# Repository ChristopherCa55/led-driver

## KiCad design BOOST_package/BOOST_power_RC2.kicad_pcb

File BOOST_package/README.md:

# BOOST LED driver: design files for PCB review

A three-channel boost LED driver on two boards, designed in KiCad 10 and simulated in LTspice 26. The boards are
meant to be made and assembled by JLCPCB.

## Boards

| Board | File | Size | Layers |
|---|---|---|---|
| Power board | `KiCad/BOOST_power_RC2.kicad_pcb` | 74 x 86 mm (18 x 12 mm corner notch) | 6 (stackup JLC061611-7628D, specified at order) |
| Control card | `KiCad/BOOST_control_RC2.kicad_pcb` | 45 x 45 mm | 6 |

The schematic for both boards is `KiCad/BOOST.kicad_sch` (open `KiCad/BOOST.kicad_pro`). Each board also has its
own schematic, linked to its PCB: open `KiCad/BOOST_power_RC2.kicad_pro` or `KiCad/BOOST_control_RC2.kicad_pro`
(Switch to PCB Editor and Update PCB work there). These hold the same parts as the main schematic, so a change goes
into both. The `.pretty` folders,
`ltspice.kicad_sym`, `fp-lib-table` and `sym-lib-table` in `KiCad/` are the project's own footprint and symbol
libraries; KiCad finds them automatically.

## KiCad notes
- Each board has its own `.kicad_pro`, which carries its net classes and design rules. Open a board through (or
  beside) its own `.kicad_pro`; without it, DRC falls back to the defaults.
- 3D models: the parts use KiCad's standard 3D library (`${KICAD10_3DMODEL_DIR}`), which comes with KiCad.

## ERC and DRC
- ERC: 0 errors, 0 warnings for the main schematic and both board projects. The card schematic has PWR_FLAGs on 5V
  and GND (they reach the card only through J11); the main schematic has none there, as U17 drives 5V.
- DRC with schematic parity: 0 on both boards.
- Power board: 0 errors, 0 unconnected. The 49 warnings are expected:
  - 46 silk over copper: a top-side logo under L1 crosses L1's middle (mechanical) pad. It is hidden under L1, and
    the gerbers cut silkscreen away from exposed pads.
  - 2 silk overlaps: the can outlines of C87/C71 and C86/C88 touch.
  - 1 library mismatch: J10's holes are drilled 1.05 mm on purpose (Samtec 0.64 mm square posts).
- Control card: 0 errors, 0 unconnected. The 1 warning is expected: a library mismatch, because J11's holes are
  drilled 1.05 mm on purpose (Samtec 0.64 mm square posts).

## LTspice
`LTspice/BOOST.asc` uses:
- custom symbols: `74HC4051.asy`, `CD4017B.asy`, `CD74HC4066.asy`, `CSS4J_4026.asy`, `INA241A4.asy`, `L78L05.asy`,
  `MC7812.asy`, `MCP4451_CTRL.asy`, `MCP4451_POT.asy`, `UCC21520.asy`;
- model libraries: `74HC4051.lib`, `CD4000_v.lib`, `CD74HC4066.lib`, `CSS4J.lib`, `HYG180N10.lib`, `INA241A4.lib`,
  `L78L05.lib`, `MC7812.lib`, `MCP4451.lib`, `MCP6561.lib`, `TLV9001.lib`, `TVS_5p0SMDJ.lib`, `UCC21520.lib`.
- The INA241A4, CD74HC4066, 74HC4051, MCP4451, L78L05, MC7812, CSS4J shunt and the 5.0SMDJ54A TVS use custom
  behavioural models written for this simulation. U16 (MC7812) uses `MC7812_TYP`, the typical dropout from
  onsemi's curve (about 1.5 V); `MC7812_WC` in the same file is a pessimistic 2 V variant.
- D28-D30 (pre-charge diodes, S2MW) use an inline `.model S2MW` directive: LTspice's 1N4007 scaled to a 2 A die
  (VF 0.91 V at 2 A; data sheet max 1.1 V). Jingdao publishes no SPICE model.
- The `LED_RED`/`LED_GREEN`/`LED_BLUE` models are unused on purpose; the LEDs use the `100W_` models.
- D19 (5.0SMDJ54A) is modelled at its minimum breakdown, 60.0 V. Over 25-30 ms it conducts in 101 of 453 switching
  cycles (22 %), 9.5 mW on average (0.15 % of its 6.5 W rating); most of its current is junction capacitance at the LX
  edges. A typical part (about 63 V) would not conduct at all in steady state.

**Parameters** (a `.param` line near the other directives):
- `IREF1_DUTY`, `IREF2_DUTY`, `IREF3_DUTY`: the Arduino's IREF PWM duty in 256ths at 490 Hz. 256 = always on (the
  default), 128 = 50 %, 0 = off.
- `POT1_CODE`, `POT2_CODE`, `POT3_CODE`: the MCP4451 wiper codes of U26A/B/C (0-256). The defaults 86/103/103 give
  2.635/2.371/2.371 A LED peaks. Code 0 is full current and 256 is zero (the pot's A terminal is grounded). At
  power-up the pot sits at mid-scale (128, about 1.98 A) until the firmware writes a code.
- Parts named `SIM_...` exist only in the simulation: the battery, cable, LEDs and the Arduino outputs.

**Results:** a 30 ms run at full duty converges in about 15-50 minutes. The `.options` line carries `solver=alt`:
with the I2C pull-ups R106 / R107 in the netlist the normal solver stops at 0.3216 ms; `solver=alt` is about 3x
slower and gives the same results. Over 25-30 ms the LEDs hold 2.635, 2.371 and
2.371 A, the outputs sit at 23.3, 33.1 and 33.1 V, and LX peaks at about 61 V.

**Start-up:** the two `.ic` lines start the servos and reference filters already settled, so the LEDs reach full
brightness within about 15 ms. Delete both lines for a true cold start (full brightness takes about half a second).
That shortcut start shows one 81 V LX spike at 0.15 ms, which real hardware does not see because it starts with the
references at zero.

**PWM dimming** (`IREFn_DUTY` below 256): each pulse keeps the full current down to about 19 % duty (red) and 25 %
(green, blue); below that the pulses carry less current. Runs can stall while all LEDs are off; the `solver=alt`
on the `.options` line gets past that.

**File size:** LTspice saves every node, so a 30 ms run writes about 22 GB (`BOOST.raw`). Make sure there is room,
or add a `.save` line that lists only the signals you want.

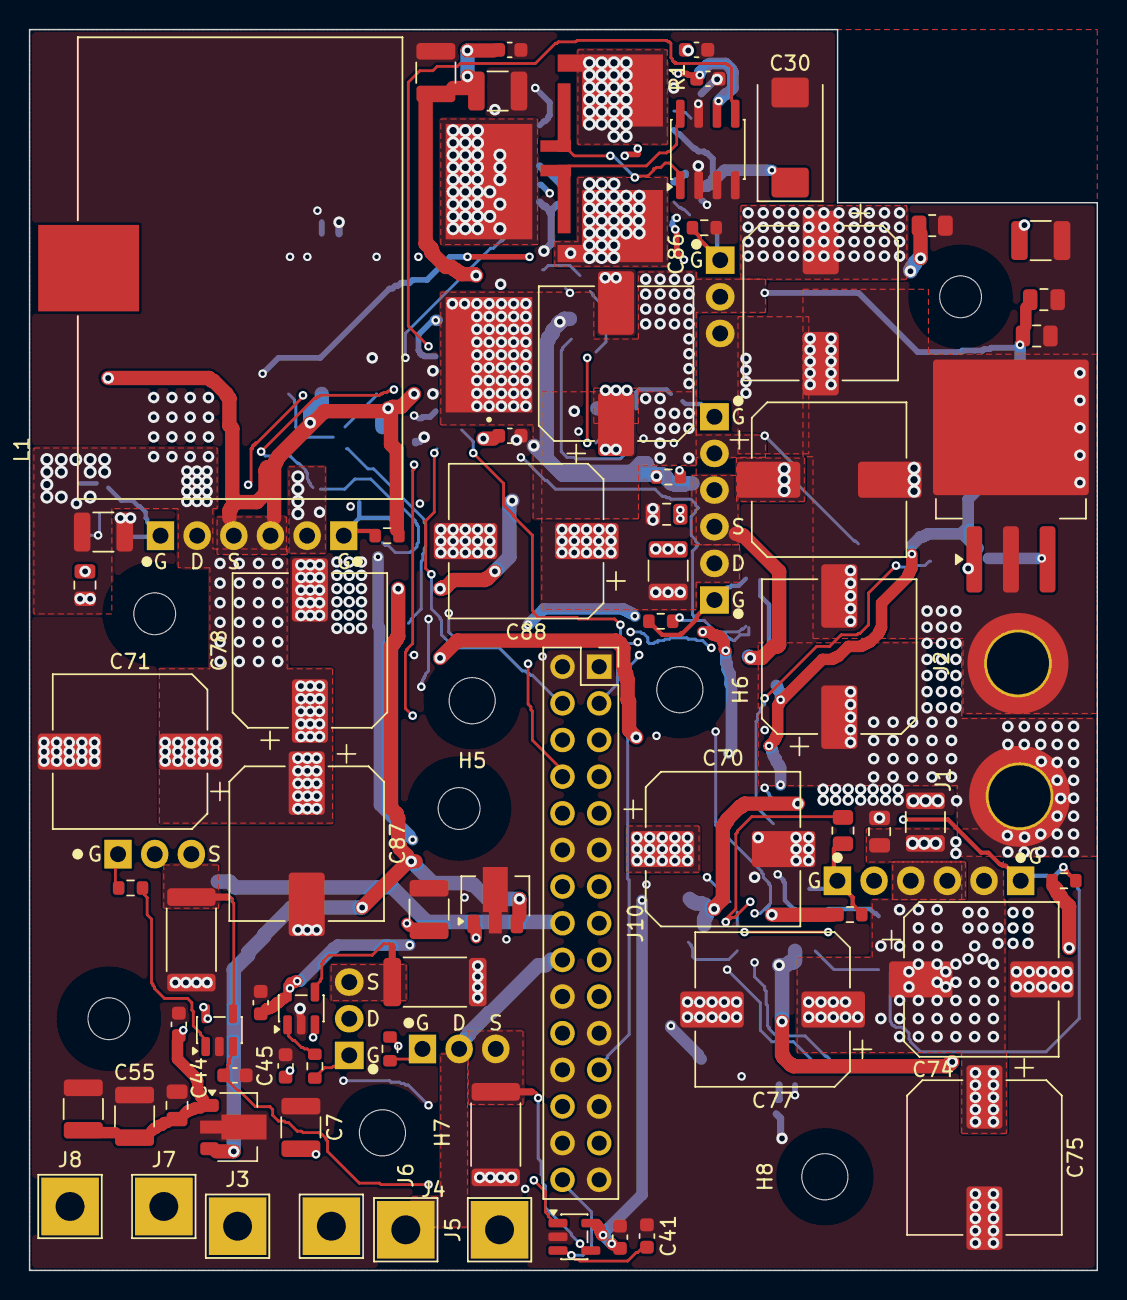
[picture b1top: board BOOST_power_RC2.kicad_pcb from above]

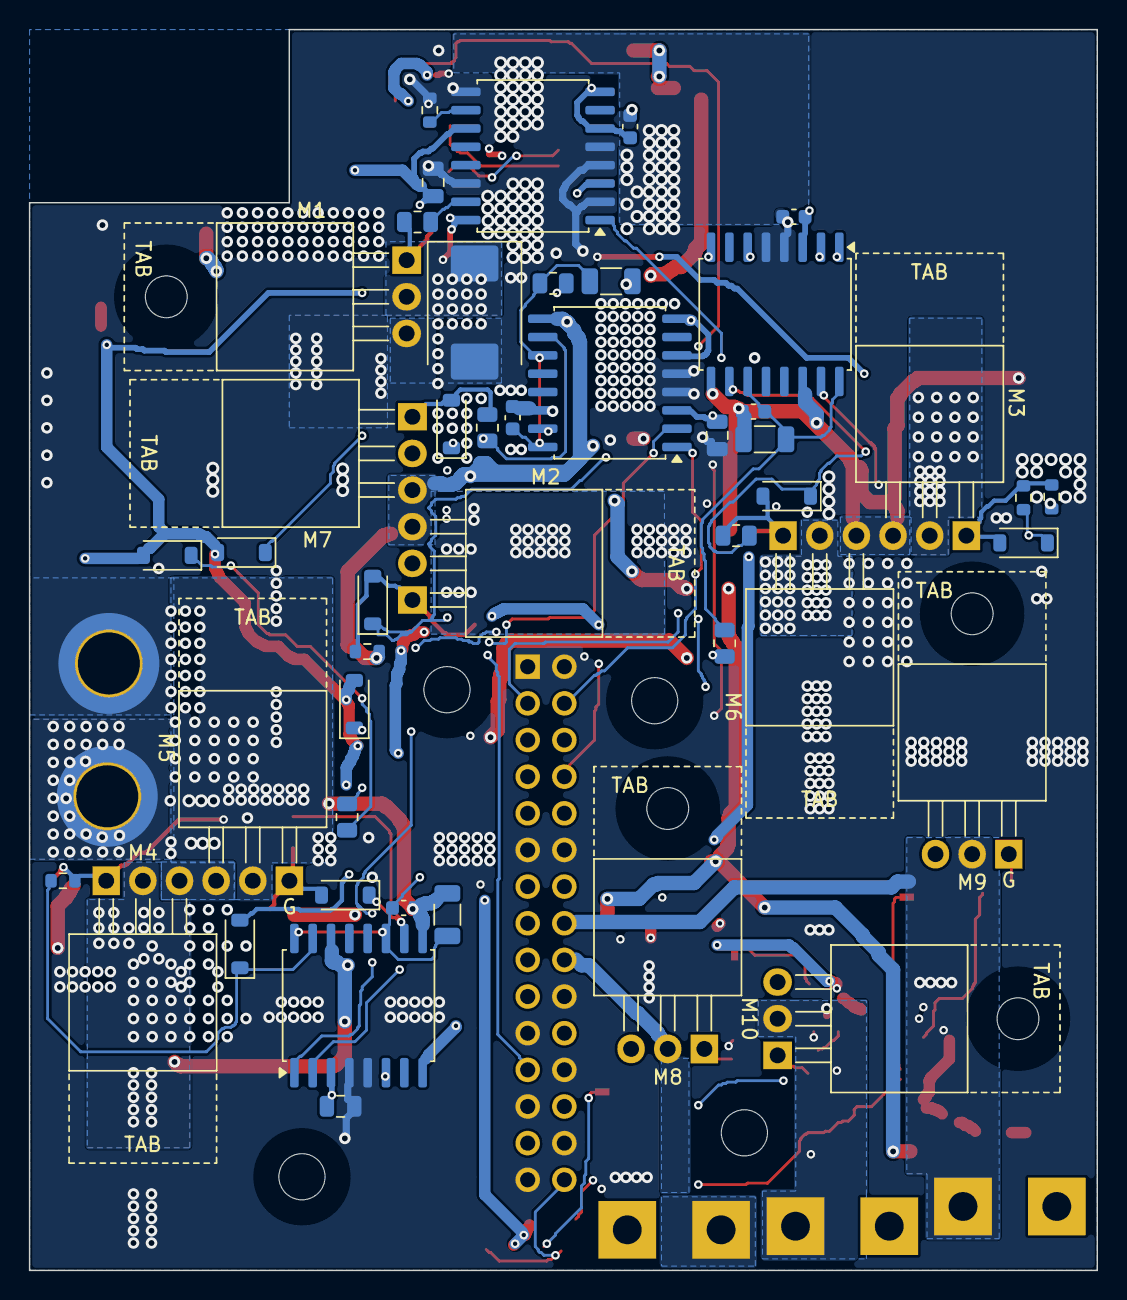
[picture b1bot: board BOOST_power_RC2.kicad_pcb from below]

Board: 8 copper layers, 74.0 x 86.0 mm, 124 parts (46 on the bottom side), 62 nets.

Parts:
C1, C4, C73: 4.7µ; C_1210_3225Metric
C3, C72, C76: 100n; C_0805_2012Metric
C6, C21, C25, C31, C62, C89: 1µ; C_0805_2012Metric
C7, C55: 22µ; C_1210_3225Metric
C16, C18, C60: 2.2µ; C_1206_3216Metric
C20, C33, C34, C35, C48, C50, C51, C61, C82, C83, C84, C90: 100n; C_0603_1608Metric
C30: 47µ; CP_EIA-7343-31_Kemet-D
C39, C56, C79, C80, C81: 10µ; C_1210_3225Metric
C40, C69, C85: 680µ; CP_Elec_10x12.5
C41, C44, C45: 1n; C_0603_1608Metric
C70, C71, C74, C75, C77, C78, C86, C87, C88: 220µ; CP_Elec_10x16.5
D2, D8, D9, D10, D11, D13, D14, D21, D22: D; D_SOD-123
D19: 5.0SMDJ54A; D_SMC
H5, H6, H7, H8: MountingHole_M3; MountingHole_3.2mm_M3
J1, J2: Conn_01x01_Pin; MountingHole_4.3mm_M4_Pad7.0_TopBottom
J3, J4, J5, J6, J7, J8: Conn_01x01_Pin; TestPoint_THTPad_4.0x4.0mm_Drill2.0mm
J10: Conn_02x15_2.54mm; PinSocket_2x15_P2.54mm_Vertical
L1: 6.8µ; IND_CSCF3218-6R8MC
M1, M8, M9, M10: HYG180N10; TO-220-3_Horizontal_TabUp_M2.5
M2, M3, M4, M5, M6, M7: HYG180N10; TO-220-3_Horizontal_TabUp_NoHole
NT1, NT2, NT3: NetTie_2; NetTie-2_SMD_Pad0.5mm
R1: 1m; R_Bourns_CSS4J-4026
R7, R52, R53: .05; R_2512_6332Metric
R13, R23, R47: 220; R_0603_1608Metric
R14: 1Meg; R_0805_2012Metric
R15: 10; R_0805_2012Metric
R21, R48, R59, R60, R70, R72: 5.1; R_0805_2012Metric
R22, R50, R56: 100; R_0603_1608Metric
R49, R61, R62, R73, R74, R75, R76, R104: 10k; R_0603_1608Metric
U1, U17: L78L05_SOT89; SOT-89-3
U6, U11, U12: MCP6241; SOT-23-5
U8, U10, U15, U19: UCC21520DW; SOIC-16W_7.5x10.3mm_P1.27mm
U16: LM2940_12; TO-263-3_TabPin2
U25: INA241A4xD; SOIC-8_3.9x4.9mm_P1.27mm

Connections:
5V: C7.1, C39.1, C48.1, C62.2, C89.2, C90.1, J10.10, U8.3 (VCCI), U8.6 (DT), U8.8 (VCCI), U10.3 (VCCI), U10.6 (DT), U10.8 (VCCI), U15.3 (VCCI), U15.6 (DT), U15.8 (VCCI), U17.1 (OUT), U19.3 (VCCI), U19.6 (DT), U19.8 (VCCI)
12V: C6.1, C25.1, C30.1, C31.1, D9.2 (+), D10.2 (+), D21.2 (+), J10.19, U16.3 (OUT), U19.11 (VDDB), U19.16 (VDDA)
Current: J10.23, U25.5
GATE_M1: M1.1, R15.2, R104.1
GATE_M2: D11.2 (+), M2.1, R13.1, R75.2
GATE_M3: D14.2 (+), M3.1, R23.2, R61.2
GATE_M4: D13.2 (+), M4.1, R47.1, R73.2
GATE_M5: D22.2 (+), M5.1, R59.1, R74.2
GATE_M6: D8.2 (+), M6.1, R49.1, R70.2
GATE_M7: D2.2 (+), M7.1, R60.2, R76.2
GND: C1.2, C3.2, C4.2, C6.2, C7.2, C20.2, C21.2, C25.2, C30.2, C31.2, C33.2, C34.2, C35.2, C39.2, C40.2, C41.2, C44.2, C45.2, C48.2, C55.2, C56.2, C62.1, C69.2, C70.2, C71.2, C72.2, C73.2, C74.2, C75.2, C76.2, C77.2, C78.2, C79.2, C80.2, C81.2, C82.2, C83.2, C84.2, C85.2, C86.2, C87.2, C88.2, C89.1, C90.2, D19.2 (+), J2.1, J10.1, J10.2, J10.11, J10.12, J10.20, J10.21, J10.24, J10.25, J10.28, J10.29, M1.3, R7.2, R14.2, R52.2, R53.2, R62.2, R104.2, U1.2 (GND), U6.2 (V-), U8.4 (GND), U8.5 (DIS), U10.4 (GND), U10.5 (DIS), U11.2 (V-), U12.2 (V-), U15.4 (GND), U15.5 (DIS), U16.2 (GND), U17.2 (GND), U19.2 (INB), U19.4 (GND), U19.5 (DIS), U19.9 (VSSB), U19.14 (VSSA), U25.2 (GND), U25.3 (REF2), U25.4 (GND), U25.7 (REF1)
IREF1_input: C45.1, J10.26, U11.3 (In+)
IREF2_input: C44.1, J10.27, U12.3 (In+)
IREF3_input: C41.1, J10.30, U6.3 (In+)
ISNS_N: R1.3, U25.1 (-)
ISNS_P: R1.2, U25.8 (+)
LX: D19.1 (-), L1.1, M1.2, M5.2, M6.2, M7.2, R14.1
M1_ON: J10.3, U19.1 (INA)
M2_ON: J10.4, U15.1 (INA)
unnamed: D2.1 (-), R60.1, U15.10 (OUTB)
unnamed: D8.1 (-), R70.1, U10.10 (OUTB)
unnamed: D9.1 (-), R48.1
unnamed: D10.1 (-), R21.1
unnamed: D11.1 (-), R13.2, U15.15 (OUTA)
unnamed: D13.1 (-), R47.2, U8.15 (OUTA)
unnamed: D14.1 (-), R23.1, U10.15 (OUTA)
unnamed: D21.1 (-), R72.1
unnamed: D22.1 (-), R59.2, U8.10 (OUTB)
unnamed: M8.1, R22.1
unnamed: M8.3, NT3.2, R7.1
unnamed: M9.1, R50.1
unnamed: M9.3, NT2.2, R53.1
unnamed: M10.1, R56.1
unnamed: M10.3, NT1.2, R52.1
unnamed: R22.2, U6.1 (OUT)
unnamed: C60.1, C61.1, R72.2, U8.11 (VDDB), U8.16 (VDDA)
unnamed: C16.1, C50.1, R48.2, U10.11 (VDDB), U10.16 (VDDA)
unnamed: R56.2, U11.1 (OUT)
unnamed: R50.2, U12.1 (OUT)
unnamed: C18.1, C51.1, R21.2, U15.11 (VDDB), U15.16 (VDDA)
unnamed: R15.1, U19.15 (OUTA)
unnamed: R62.1, U19.10 (OUTB)
Output1_drain: J4.1 (Pin_1_1), J10.14, M10.2
Output2_drain: J7.1 (Pin_1_1), J10.16, M9.2
Output3_drain: J6.1 (Pin_1_1), J10.18, M8.2
SNS_CH1: NT1.1, U11.4 (In-)
SNS_CH2: NT2.1, U12.4 (In-)
SNS_CH3: NT3.1, U6.4 (In-)
Vin: C40.1, C69.1, C79.1, C80.1, C81.1, C82.1, C83.1, C84.1, C85.1, J1.1, R1.1, U1.3 (IN), U16.1 (IN), U17.3 (IN)
Vout_1: C1.1, C70.1, C72.1, C86.1, C88.1, J3.1 (Pin_1_1), J10.13, M2.2
Vout_2: C3.1, C71.1, C73.1, C78.1, C87.1, J8.1 (Pin_1_1), J10.15, M3.2
Vout_3: C4.1, C74.1, C75.1, C76.1, C77.1, J5.1 (Pin_1_1), J10.17, M4.2
analog_5V: C20.1, C21.1, C33.1, C34.1, C35.1, C55.1, C56.1, J10.22, U1.1 (OUT), U6.5 (V+), U11.5 (V+), U12.5 (V+), U25.6 (V+)
ena_out_1: J10.5, U15.2 (INB)
ena_out_2: J10.7, U10.2 (INB)
ena_out_3: J10.9, U8.2 (INB)
m2_source: C18.2, C51.2, M2.3, M7.3, R75.1, R76.1, U15.9 (VSSB), U15.14 (VSSA)
m3_source: C16.2, C50.2, M3.3, M6.3, R49.2, R61.1, U10.9 (VSSB), U10.14 (VSSA)
m4_source: C60.2, C61.2, M4.3, M5.3, R73.1, R74.1, U8.9 (VSSB), U8.14 (VSSA)
out_2_on: J10.6, U10.1 (INA)
out_3_on: J10.8, U8.1 (INA)
rsense_lo: L1.2, R1.4

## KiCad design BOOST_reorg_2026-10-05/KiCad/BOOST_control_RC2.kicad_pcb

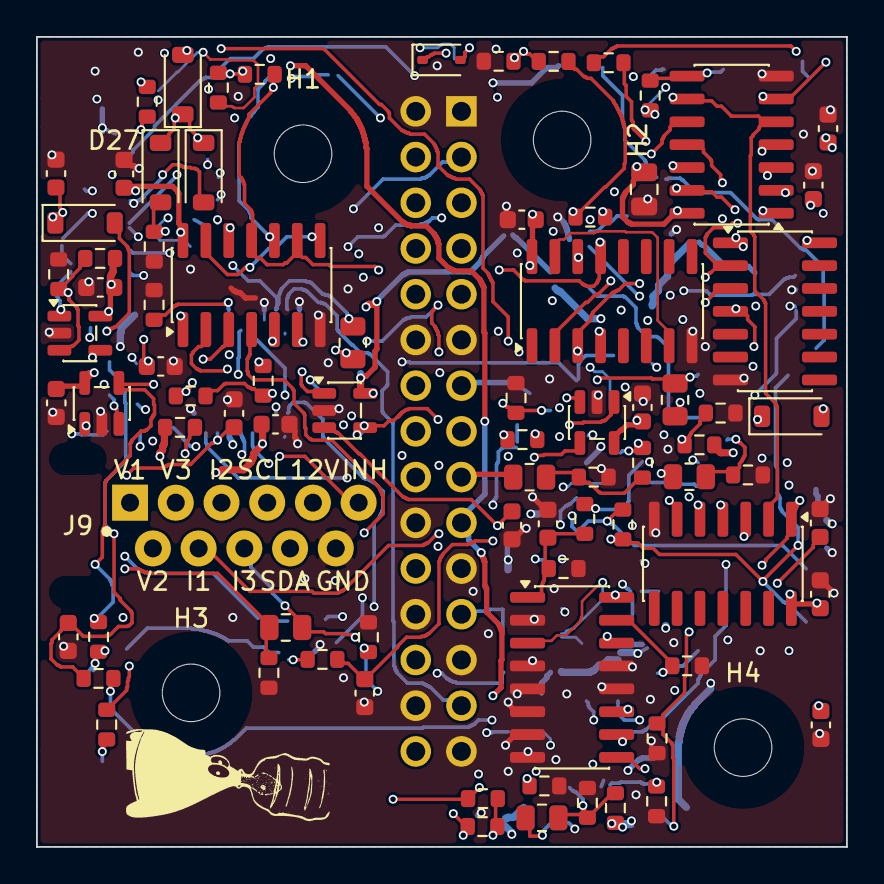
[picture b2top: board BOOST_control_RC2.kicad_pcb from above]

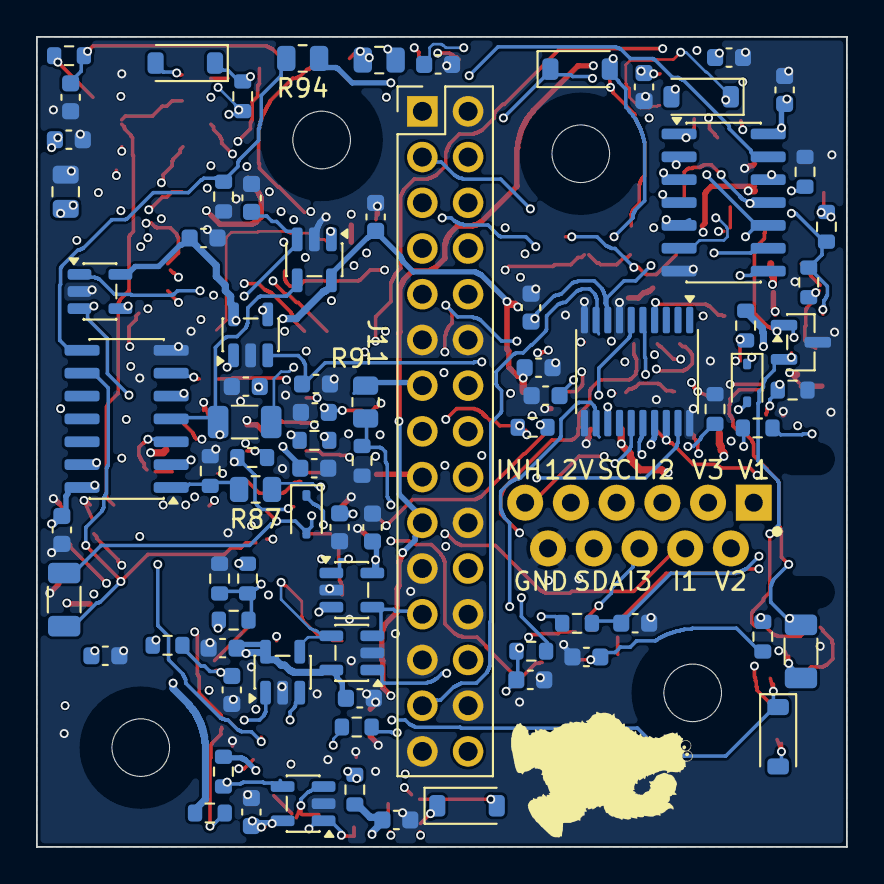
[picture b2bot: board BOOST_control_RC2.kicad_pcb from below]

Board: 6 copper layers, 45.0 x 45.0 mm, 166 parts (81 on the bottom side), 105 nets.

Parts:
C8, C9, C17, C19: 330p; C_0603_1608Metric
C10, C11, C13: 4.7n; C_0603_1608Metric
C12, C22, C23, C24, C26, C28, C29, C32, C36, C37, C38, C42, C43, C46, C52, C53, C54, C58, C59, C63, C65, C66, C68, C92, C94, C95, C96, C97, C98, C99, C104: 100n; C_0603_1608Metric
C14: 220p; C_0603_1608Metric
C15: 100p; C_0603_1608Metric
C47, C93, C103: 10u; C_0603_1608Metric
C49, C64, C67: 100n; C_1206_3216Metric
C57, C91: 1µ; C_0805_2012Metric
C100, C101, C102: 1n; C_0603_1608Metric
D1, D3, D4, D5, D6, D7, D15, D20, D24, D27: D; D_SOD-123
D23, D25, D26: D; D_SOD-323
H1, H2, H3, H4: MountingHole_M3; MountingHole_3.2mm_M3
J9: Conn_01x11; WirePads_11_Staggered_P1.27mm_Drill1.0mm_TieSlots
J11: Conn_02x15_2.54mm; PinHeader_2x15_P2.54mm_Vertical
Q1: PNP; SOT-23
R2, R6, R31, R33, R39, R41, R67, R77, R83, R85, R99, R100, R101, R102, R103: 10k; R_0603_1608Metric
R3, R32, R40: 620k; R_0603_1608Metric
R4, R54, R55, R58, R71: 1k; R_0603_1608Metric
R8, R34, R42, R51, R63, R78, R80: 2k; R_0603_1608Metric
R9, R35, R43: 18k; R_0805_2012Metric
R11, R17: 510k; R_0603_1608Metric
R16, R19: 5.1k; R_0603_1608Metric
R18, R20: 200k; R_0603_1608Metric
R25, R87, R94: 910k; R_0805_2012Metric
R26, R64, R79, R81: 220; R_0603_1608Metric
R27, R37, R45: 4.7k; R_0603_1608Metric
R28, R36, R38, R44, R46, R88, R91, R95, R96, R105: 100k; R_0603_1608Metric
R29, R30, R57: 22k; R_0805_2012Metric
R65: 22k; R_0603_1608Metric
R66, R89, R92, R97: 3.3k; R_0603_1608Metric
R68: 62k; R_0603_1608Metric
R69: 20k; R_0603_1608Metric
R82: 56k; R_0603_1608Metric
R84: 120k; R_0603_1608Metric
R86: 1Meg; R_0805_2012Metric
R90, R93, R98: 10Meg; R_0603_1608Metric
U2, U4, U5, U14, U21: MCP6561; SOT-23-5
U3, U7, U13, U22, U23, U24: TLV9001; SOT-23-5
U18: 4017; SOIC-16_3.9x9.9mm_P1.27mm
U26: MCP4451-103E/ST; TSSOP-20_4.4x6.5mm_P0.65mm
U28: 74HC4051; SOIC-16_3.9x9.9mm_P1.27mm
U101, U102, U103: 74HC00; SOIC-14_3.9x8.7mm_P1.27mm
U104, U105: 74HC14; SOIC-14_3.9x8.7mm_P1.27mm
U106: CD74HC4066; SOIC-14_3.9x8.7mm_P1.27mm

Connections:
0A_hi: R11.1, U2.1 (OUT), U101.2 (B)
0err_hi: D1.2 (+), D3.1 (-), R18.1, R66.1, U4.1 (OUT), U104.11 (A)
5V: C12.1, C22.1, C23.1, C24.1, C26.1, C28.1, C29.1, C52.1, C53.2, C54.1, C57.2, C58.1, C91.2, C92.1, C94.1, C95.1, C96.1, C97.1, C98.1, C99.1, C104.1, J11.10, R17.2, R20.2, R69.2, R82.1, R103.1, U2.5 (V+), U4.5 (V+), U5.5 (V+), U14.5 (V+), U18.16 (VDD), U21.5 (V+), U26.17 (VDD), U28.16 (VCC), U101.14 (VCC), U102.14 (VCC), U103.14 (VCC), U104.14 (VCC), U105.14 (VCC), U106.14 (VDD)
12V: J9.9, J11.19, R84.1
.1Vout_1: R2.2, R8.1, R9.1
.1Vout_2: R31.2, R34.1, R35.1
.1Vout_3: R39.2, R42.1, R43.1
.1Vref_1: C46.1, D26.1 (-), R6.2, U3.3 (In+)
.1Vref_2: C43.1, D25.1 (-), R33.2, U7.3 (In+)
.1Vref_3: C42.1, D23.1 (-), R41.2, U13.3 (In+)
ARD_M1_INHIBIT: D27.2, J9.11, R105.1
Current: J11.23, U2.4 (In-), U5.3 (In+)
GND: C8.1, C9.1, C10.1, C11.1, C12.2, C13.1, C14.2, C15.2, C17.1, C19.2, C22.2, C23.2, C24.2, C26.2, C28.2, C29.2, C32.2, C36.1, C37.1, C38.1, C42.2, C43.2, C46.2, C47.2, C52.2, C53.1, C54.2, C57.1, C58.2, C59.2, C63.2, C65.2, C66.2, C68.2, C91.1, C92.2, C93.2, C94.2, C95.2, C96.2, C97.2, C98.2, C99.2, C100.2, C101.2, C102.2, C103.2, C104.2, J9.10, J11.1, J11.2, J11.11, J11.12, J11.20, J11.21, J11.24, J11.25, J11.28, J11.29, Q1.3 (C), R8.2, R16.2, R19.2, R28.1, R34.2, R36.2, R38.1, R42.2, R46.1, R54.2, R55.2, R58.2, R68.2, R83.2, R85.2, R88.2, R89.2, R92.2, R95.2, R97.2, R99.2, R102.2, R105.2, U2.2 (V-), U3.2 (V-), U4.2 (V-), U5.2 (V-), U7.2 (V-), U13.2 (V-), U14.2 (V-), U18.8 (VSS), U21.2 (V-), U22.2 (V-), U23.2 (V-), U24.2 (V-), U26.7 (VSS), U26.10 (P1A), U26.11 (P0A), U26.20 (P2A), U28.2 (A6), U28.4 (A7), U28.5 (A5), U28.6 (~E), U28.7 (VEE), U28.8 (GND), U28.12 (A3), U28.13 (A0), U101.7 (GND), U102.7 (GND), U103.7 (GND), U104.7 (GND), U105.7 (GND), U106.7 (VSS)
IREF1: J9.4, R29.1, U106.6 (CTRL)
IREF1_input: J11.26, U26.12 (P0W)
IREF2: J9.5, R30.1, U106.5 (CTRL)
IREF2_input: J11.27, U26.9 (P1W)
IREF3: J9.6, R57.1, U106.13 (CTRL)
IREF3_input: J11.30, U26.19 (P2W)
M1_INHIBIT: D1.1 (-), D15.1 (-), D24.1 (-), D27.1, R26.1, U104.1 (A)
M1_ON: J11.3, U101.5 (B), U104.2 (Y)
M2_ON: J11.4, U104.4 (Y)
unnamed: C8.2, R63.1, R64.1
unnamed: C9.2, R78.1, R79.1
unnamed: C17.2, R80.1, R81.1
unnamed: C19.1, R26.2, R51.2
unnamed: D3.2 (+), R65.2
unnamed: D4.2 (+), Q1.1 (B), R65.1
unnamed: C15.1, D4.1 (-), R71.1
unnamed: D5.2 (+), R63.2, U103.3 (Y)
unnamed: D5.1 (-), R64.2, U105.3 (A)
unnamed: D7.2 (+), R78.2, U102.8 (Y)
unnamed: D7.1 (-), R79.2, U104.13 (A)
unnamed: D20.2 (+), R80.2, U102.6 (Y)
unnamed: D20.1 (-), R81.2, U105.1 (A)
unnamed: C49.2, D23.2 (+), R90.2, U22.1 (OUT)
unnamed: D24.2 (+), R86.1, U21.1 (OUT)
unnamed: C64.2, D25.2 (+), R93.2, U23.1 (OUT)
unnamed: C67.2, D26.2 (+), R98.2, U24.1 (OUT)
unnamed: C14.1, Q1.2 (E), R66.2, U14.4 (In-)
unnamed: R11.2, R16.1, R17.1, U2.3 (In+)
unnamed: R2.1, R3.2, U3.4 (In-)
unnamed: R18.2, R19.1, R20.1, U4.3 (In+)
unnamed: R31.1, R32.2, U7.4 (In-)
unnamed: R39.1, R40.2, U13.4 (In-)
unnamed: R67.2, R68.1, R69.1, U14.3 (In+)
unnamed: U18.7 (Q3), U18.15 (Reset)
unnamed: R82.2, R85.1, R86.2, U21.3 (In+)
unnamed: R83.1, R84.2, U21.4 (In-)
unnamed: C59.1, R44.2, R89.1, U22.3 (In+)
unnamed: C65.1, R91.2, R92.1, U23.3 (In+)
unnamed: C68.1, R96.2, R97.1, U24.3 (In+)
unnamed: C100.1, R29.2, R54.1, U26.13 (P0B)
unnamed: C101.1, R30.2, R55.1, U26.8 (P1B)
unnamed: C102.1, R57.2, R58.1, U26.18 (P2B)
unnamed: R99.1, U26.16 (A1)
unnamed: R102.1, U26.4 (HVC/A0)
unnamed: R103.2, U26.15 (~RESET)
unnamed: R4.2, U101.3 (Y)
unnamed: U102.3 (Y), U104.3 (A)
unnamed: U102.11 (Y), U104.5 (A)
unnamed: U103.6 (Y), U104.9 (A)
unnamed: R87.2, R88.1, U106.1 (A)
unnamed: C49.1, R90.1, U22.4 (In-), U106.2 (B)
unnamed: R25.2, R36.1, U106.3 (A)
unnamed: C64.1, R93.1, U23.4 (In-), U106.4 (B)
unnamed: R94.2, R95.1, U106.8 (A)
unnamed: C67.1, R98.1, U24.4 (In-), U106.9 (B)
Out: U101.8 (Y), U101.13 (A)
Out-: D15.2 (+), R51.1, U18.13 (CKEN), U101.9 (B), U101.11 (Y), U102.1 (A), U102.13 (A), U103.5 (B)
Output1_drain: J11.14, R94.1
Output2_drain: J11.16, R25.1
Output3_drain: J11.18, R87.1
RESET-: U101.6 (Y), U101.12 (B)
Reset_raw: U5.1 (OUT), U101.4 (A)
SCL: J9.7, U26.5 (SCL)
SDA: J9.8, U26.6 (SDA)
U102B_A: U18.3 (Q0), U28.11 (S0), U102.4 (A)
U102C_A: U18.2 (Q1), U28.10 (S1), U102.10 (A)
U103A_A: U18.4 (Q2), U28.9 (S2), U103.1 (A)
V_err: U4.4 (In-), U5.4 (In-), U28.3 (A)
Verr1: C13.2, R27.2, R28.2, U28.14 (A1)
Verr2: C11.2, R37.2, R38.2, U28.15 (A2)
Verr3: C10.2, R45.2, R46.2, U28.1 (A4)
VerrGT0: U101.1 (A), U102.5 (B), U102.9 (B), U103.2 (B), U104.10 (Y)
Voltage_err_1: R3.1, R27.1, U3.1 (OUT)
Voltage_err_2: R32.1, R37.1, U7.1 (OUT)
Voltage_err_3: R40.1, R45.1, U13.1 (OUT)
Vout_1: J11.13, R9.2
Vout_2: J11.15, R35.2
Vout_3: J11.17, R43.2
Vref_1: C103.1, R6.1, R101.2
Vref_1_arduino: J9.1, R101.1
Vref_2: C93.1, R33.1, R100.2
Vref_2_arduino: J9.2, R100.1
Vref_3: C47.1, R41.1, R77.2
Vref_3_arduino: J9.3, R77.1
analog_5V: C32.1, C36.2, C37.2, C38.2, C63.1, C66.1, J11.22, R44.1, R91.1, R96.1, U3.5 (V+), U7.5 (V+), U13.5 (V+), U22.5 (V+), U23.5 (V+), U24.5 (V+)
ena_out_1: J11.5, U102.2 (B), U105.2 (Y)
ena_out_2: J11.7, U102.12 (B), U104.12 (Y)
ena_out_3: J11.9, U103.4 (A), U105.4 (Y)
low_error_timeout: D6.1 (-), R67.1, R71.2, U14.1 (OUT), U18.14 (CLK)
out_2_on: J11.6, U104.6 (Y)
out_3_on: J11.8, U104.8 (Y)
set-: D6.2 (+), R4.1, U101.10 (A)

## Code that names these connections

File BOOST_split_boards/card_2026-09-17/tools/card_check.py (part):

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Reads the placer config and a layout. Reports:
- legality in the placer's model: courtyard overlaps per side (through-hole parts on both), parts outside the card,
  mounting-hole keep-out intrusions (KiCad DRC on the saved board is the final word);
- the analog constraints: the Current net (J11.23 -> U2.4, U5.3), its distance to the 74HC14s, M1_ON and I2C,
  D27 / R105 at the M1_INHIBIT node;
- decoupling: each IC supply pin to its nearest capacitor on the rail;
- J9's pins to their first load;
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# analog
L.append('## Analog constraints\n')
L.append('| Item | Value |\n|---|---|')
cur = [p for p in netpins.get('Current', []) if p in pin]
for p in cur:
    if p != 'J11.23':
        L.append('| Current: J11.23 -> %s | %.1f mm straight, %s side |' % (p, d('J11.23', p), lay[p.split('.')[0]][3]))
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L.append('| Current net half-perimeter | %.1f mm |' % ((max(xs) - min(xs)) + (max(ys) - min(ys))))
for grp, members in (('74HC14 U104', [p for p in pin if p.startswith('U104.')]),
                     ('74HC14 U105', [p for p in pin if p.startswith('U105.')]),
                     ('M1_ON', [p for p in netpins.get('M1_ON', []) if p in pin]),
                     ('SCL', [p for p in netpins.get('SCL', []) if p in pin]),
                     ('SDA', [p for p in netpins.get('SDA', []) if p in pin])):
    best = min((d(a, b), a, b) for a in cur for b in members)
    L.append('| Current pins to %s | %.1f mm (%s - %s) |' % (grp, best[0], best[1], best[2]))
for a, b, m, w in cfg.get('near', []):
    L.append('| %s -> %s | %.1f mm (limit %.1f) |' % (a, b, d(a, b), m))

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            '+'.join(vic), g, best[0], best[1], best[2], m, '' if best[0] >= m - 1e-6 else ' **short**'))
for r, sd in cfg.get('side_only', {}).items():
    L.append('| %s restricted to %s | on %s |' % (r, sd, lay[r][3]))
mi = [p for p in netpins.get('M1_INHIBIT', []) if p in pin]
L.append('| M1_INHIBIT node spread (%s) | %.1f mm half-perimeter |' % (
    ', '.join(mi), (max(pin[p][0] for p in mi) - min(pin[p][0] for p in mi)) +
    (max(pin[p][1] for p in mi) - min(pin[p][1] for p in mi))))
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        ax.set_aspect('equal')
        ax.set_title('%s side (%s)%s' % ('top' if sd == 'F' else 'underside', sd,
                                        ' - seen from the top' if sd == 'B' else ''))
    fig.suptitle('Control card placement (nets as minimum spanning trees of their pins): red Current and U2 In+, '
                 'magenta V_err, purple I2C,' + chr(10) + 'orange M1_ON, olive other 74HC14 outputs, brown M1_INHIBIT; '
                 'red circles = output cans below; blue = H1-H4 keep-outs')
    fig.savefig(PNG, dpi=120, bbox_inches='tight')
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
